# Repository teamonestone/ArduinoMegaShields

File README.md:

# Arduino Mega Shields
Shields for the Arduino Mega.

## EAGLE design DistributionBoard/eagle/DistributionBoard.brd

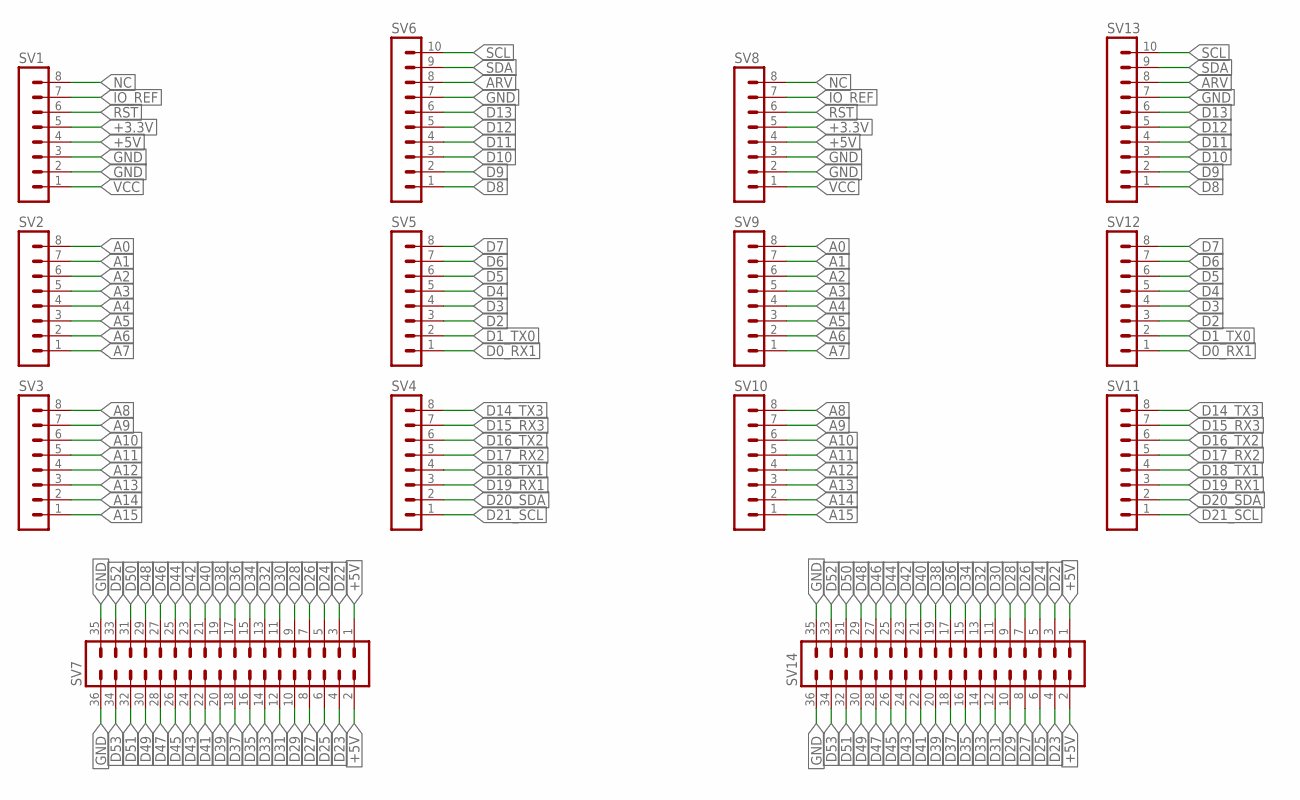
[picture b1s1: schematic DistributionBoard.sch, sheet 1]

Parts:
SV1, SV2, SV3, SV4, SV5, SV8, SV9, SV10, SV11, SV12: MA08-1
SV6, SV13: MA10-1
SV7, SV14: MA18-2

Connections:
+3.3V: SV1.5, SV8.5
+5V: SV1.4, SV7.1, SV7.2, SV8.4, SV14.1, SV14.2; also elsewhere on the board
A0: SV2.8, SV9.8
A1: SV2.7, SV9.7
A2: SV2.6, SV9.6
A3: SV2.5, SV9.5
A4: SV2.4, SV9.4
A5: SV2.3, SV9.3
A6: SV2.2, SV9.2
A7: SV2.1, SV9.1
A8: SV3.8, SV10.8
A9: SV3.7, SV10.7
A10: SV3.6, SV10.6; also elsewhere on the board
A11: SV3.5, SV10.5; also elsewhere on the board
A12: SV3.4, SV10.4; also elsewhere on the board
A13: SV3.3, SV10.3; also elsewhere on the board
A14: SV3.2, SV10.2; also elsewhere on the board
A15: SV3.1, SV10.1; also elsewhere on the board
ARV: SV6.8, SV13.8
D0_RX1: SV5.1, SV12.1
D1_TX0: SV5.2, SV12.2
D2: SV5.3, SV12.3
D3: SV5.4, SV12.4
D4: SV5.5, SV12.5
D5: SV5.6, SV12.6
D6: SV5.7, SV12.7
D7: SV5.8, SV12.8
D8: SV6.1, SV13.1
D9: SV6.2, SV13.2; also elsewhere on the board
D10: SV6.3, SV13.3; also elsewhere on the board
D11: SV6.4, SV13.4; also elsewhere on the board
D12: SV6.5, SV13.5; also elsewhere on the board
D13: SV6.6, SV13.6
D14_TX3: SV4.8, SV11.8
D15_RX3: SV4.7, SV11.7
D16_TX2: SV4.6, SV11.6
D17_RX2: SV4.5, SV11.5
D18_TX1: SV4.4, SV11.4
D19_RX1: SV4.3, SV11.3
D20_SDA: SV4.2, SV11.2; also elsewhere on the board
D21_SCL: SV4.1, SV11.1; also elsewhere on the board
D22: SV7.3, SV14.3
D23: SV7.4, SV14.4
D24: SV7.5, SV14.5
D25: SV7.6, SV14.6
D26: SV7.7, SV14.7
D27: SV7.8, SV14.8
D28: SV7.9, SV14.9; also elsewhere on the board
D29: SV7.10, SV14.10; also elsewhere on the board
D30: SV7.11, SV14.11; also elsewhere on the board
D31: SV7.12, SV14.12; also elsewhere on the board
D32: SV7.13, SV14.13; also elsewhere on the board
D33: SV7.14, SV14.14; also elsewhere on the board
D34: SV7.15, SV14.15; also elsewhere on the board
D35: SV7.16, SV14.16; also elsewhere on the board
D36: SV7.17, SV14.17; also elsewhere on the board
D37: SV7.18, SV14.18; also elsewhere on the board
D38: SV7.19, SV14.19
D39: SV7.20, SV14.20
D40: SV7.21, SV14.21; also elsewhere on the board
D41: SV7.22, SV14.22; also elsewhere on the board
D42: SV7.23, SV14.23; also elsewhere on the board
D43: SV7.24, SV14.24; also elsewhere on the board
D44: SV7.25, SV14.25; also elsewhere on the board
D45: SV7.26, SV14.26; also elsewhere on the board
D46: SV7.27, SV14.27; also elsewhere on the board
D47: SV7.28, SV14.28; also elsewhere on the board
D48: SV7.29, SV14.29; also elsewhere on the board
D49: SV7.30, SV14.30; also elsewhere on the board
D50: SV7.31, SV14.31; also elsewhere on the board
D51: SV7.32, SV14.32; also elsewhere on the board
D52: SV7.33, SV14.33; also elsewhere on the board
D53: SV7.34, SV14.34
GND: SV1.2, SV1.3, SV6.7, SV7.35, SV7.36, SV8.2, SV8.3, SV13.7, SV14.35, SV14.36; also elsewhere on the board
IO_REF: SV1.7, SV8.7
NC: SV1.8, SV8.8
RST: SV1.6, SV8.6; also elsewhere on the board
SCL: SV6.10, SV13.10
SDA: SV6.9, SV13.9
VCC: SV1.1, SV8.1; also elsewhere on the board

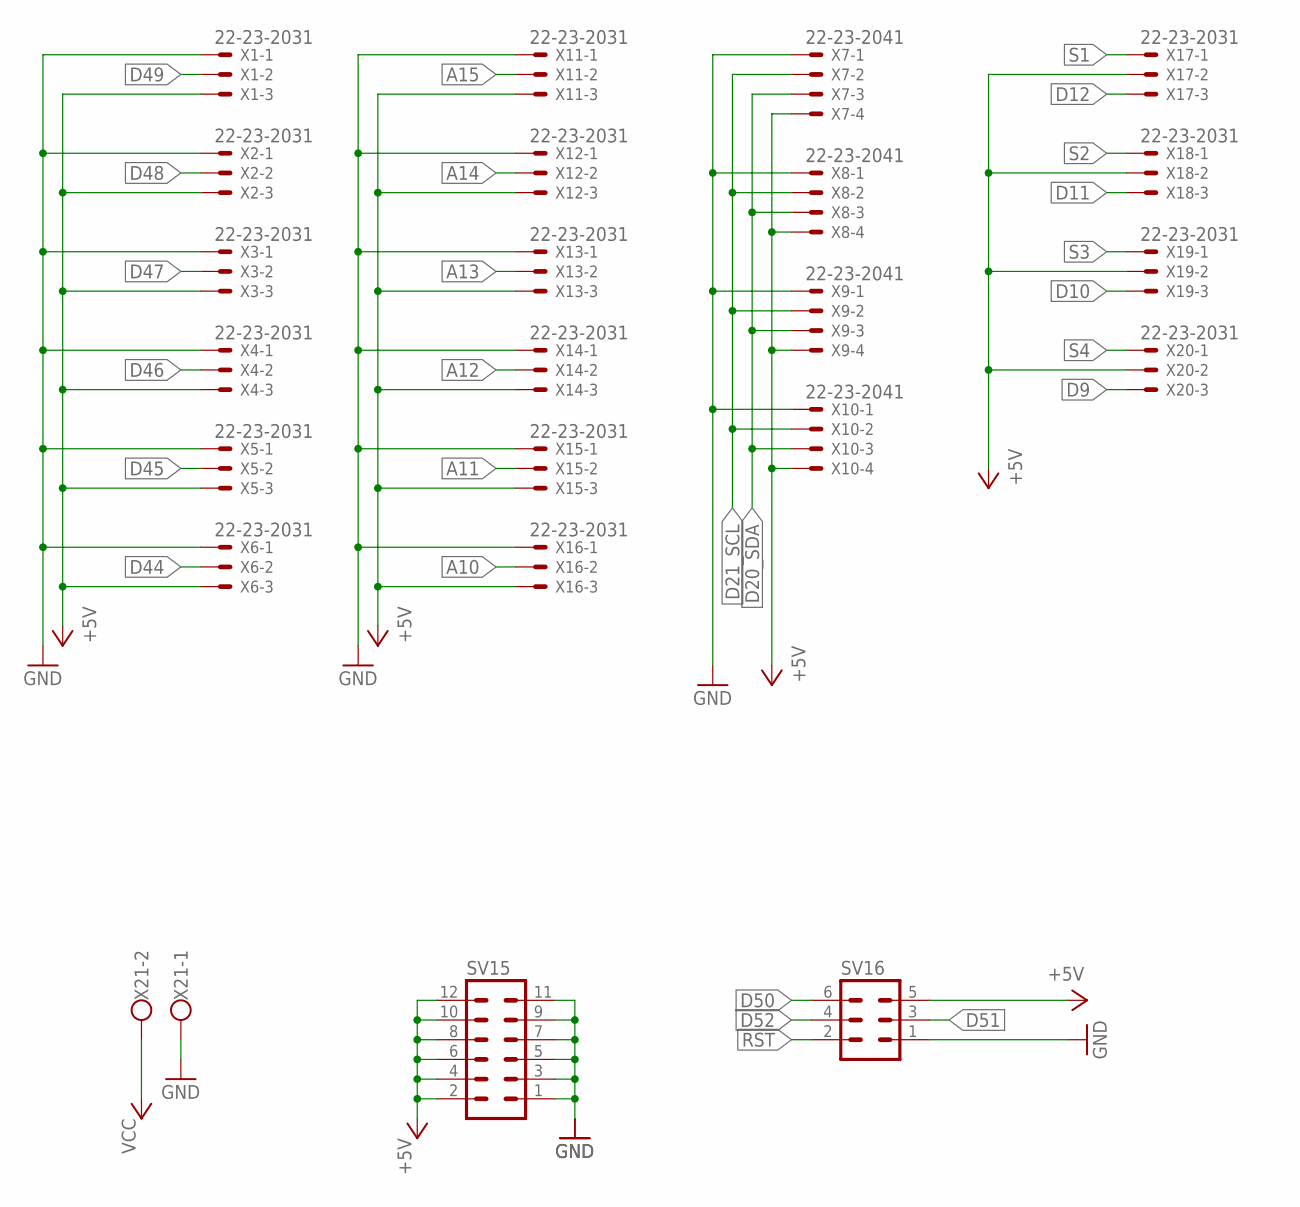
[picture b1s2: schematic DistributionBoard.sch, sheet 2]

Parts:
SV15: MA06-2
SV16: MA03-2
X1, X2, X3, X4, X5, X6, X11, X12, X13, X14, X15, X16, X17, X18, X19, X20: 22-23-2031
X7, X8, X9, X10: 22-23-2041
X21: W237-102

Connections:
+5V: SV15.2, SV15.4, SV15.6, SV15.8, SV15.10, SV15.12, SV16.5, X1.3, X2.3, X3.3, X4.3, X5.3, X6.3, X7.4, X8.4, X9.4, X10.4, X11.3, X12.3, X13.3, X14.3, X15.3, X16.3, X17.2, X18.2, X19.2, X20.2; also elsewhere on the board
A10: X16.2; also elsewhere on the board
A11: X15.2; also elsewhere on the board
A12: X14.2; also elsewhere on the board
A13: X13.2; also elsewhere on the board
A14: X12.2; also elsewhere on the board
A15: X11.2; also elsewhere on the board
D9: X20.3; also elsewhere on the board
D10: X19.3; also elsewhere on the board
D11: X18.3; also elsewhere on the board
D12: X17.3; also elsewhere on the board
D20_SDA: X7.3, X8.3, X9.3, X10.3; also elsewhere on the board
D21_SCL: X7.2, X8.2, X9.2, X10.2; also elsewhere on the board
D44: X6.2; also elsewhere on the board
D45: X5.2; also elsewhere on the board
D46: X4.2; also elsewhere on the board
D47: X3.2; also elsewhere on the board
D48: X2.2; also elsewhere on the board
D49: X1.2; also elsewhere on the board
D50: SV16.6; also elsewhere on the board
D51: SV16.3; also elsewhere on the board
D52: SV16.4; also elsewhere on the board
GND: SV15.1, SV15.3, SV15.5, SV15.7, SV15.9, SV15.11, SV16.1, X1.1, X2.1, X3.1, X4.1, X5.1, X6.1, X7.1, X8.1, X9.1, X10.1, X11.1, X12.1, X13.1, X14.1, X15.1, X16.1, X21.1; also elsewhere on the board
RST: SV16.2; also elsewhere on the board
S1: X17.1; also elsewhere on the board
S2: X18.1; also elsewhere on the board
S3: X19.1; also elsewhere on the board
S4: X20.1; also elsewhere on the board
VCC: X21.2; also elsewhere on the board

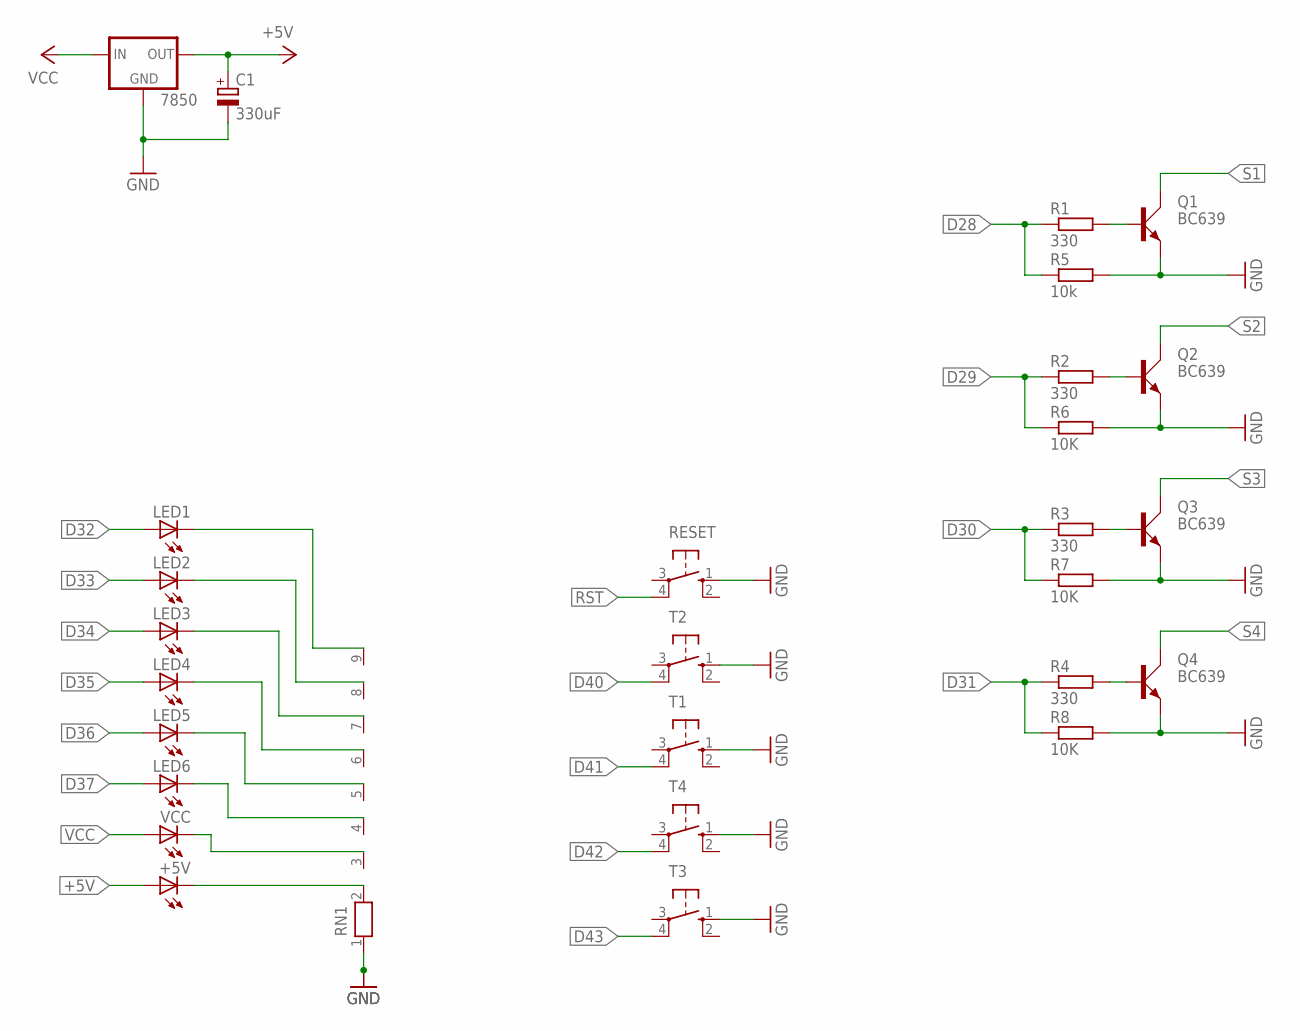
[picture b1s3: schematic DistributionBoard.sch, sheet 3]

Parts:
7850: 78XXS
+5V: LED3MM
C1: 330uF; E3,5-8
LED1, LED2, LED3, LED4, LED5, LED6: LED3MM
Q1, Q2, Q3, Q4: BC639; SOT54D
R1, R2, R3, R4: 330; M1206
R5: 10k; M1206
R6, R7, R8: 10K; M1206
RESET: 10-XX; B3F-10XX
RN1: RN08; RN-9
T1, T2, T3, T4: 10-XX; B3F-10XX
VCC: LED3MM

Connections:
+5V: 7850.OUT, +5V.A, C1.+; also elsewhere on the board
D28: R1.1, R5.1; also elsewhere on the board
D29: R2.1, R6.1; also elsewhere on the board
D30: R3.1, R7.1; also elsewhere on the board
D31: R4.1, R8.1; also elsewhere on the board
D32: LED1.A; also elsewhere on the board
D33: LED2.A; also elsewhere on the board
D34: LED3.A; also elsewhere on the board
D35: LED4.A; also elsewhere on the board
D36: LED5.A; also elsewhere on the board
D37: LED6.A; also elsewhere on the board
D40: T2.4 (P1); also elsewhere on the board
D41: T1.4 (P1); also elsewhere on the board
D42: T4.4 (P1); also elsewhere on the board
D43: T3.4 (P1); also elsewhere on the board
GND: 7850.GND, C1.-, Q1.E, Q2.E, Q3.E, Q4.E, R5.2, R6.2, R7.2, R8.2, RESET.1 (S), RN1.1, T1.1 (S), T2.1 (S), T3.1 (S), T4.1 (S); also elsewhere on the board
unnamed: +5V.K (C), RN1.2
unnamed: RN1.3, VCC.K (C)
unnamed: LED6.K (C), RN1.4
unnamed: LED5.K (C), RN1.5
unnamed: LED4.K (C), RN1.6
unnamed: LED3.K (C), RN1.7
unnamed: LED2.K (C), RN1.8
unnamed: LED1.K (C), RN1.9
unnamed: Q4.B, R4.2
unnamed: Q3.B, R3.2
unnamed: Q2.B, R2.2
unnamed: Q1.B, R1.2
RST: RESET.4 (P1); also elsewhere on the board
S1: Q1.C; also elsewhere on the board
S2: Q2.C; also elsewhere on the board
S3: Q3.C; also elsewhere on the board
S4: Q4.C; also elsewhere on the board
VCC: 7850.IN, VCC.A; also elsewhere on the board

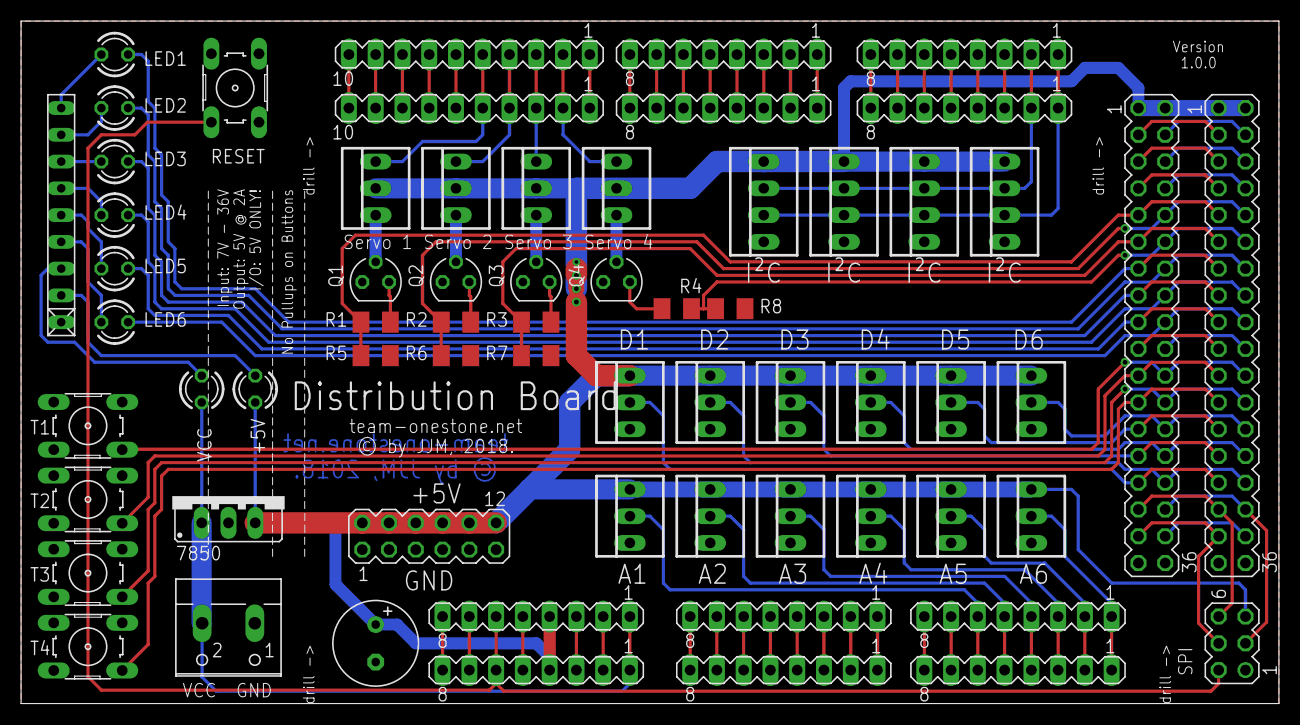
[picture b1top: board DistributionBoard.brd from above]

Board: 2 copper layers, 119.4 x 64.8 mm, 65 parts (0 on the bottom side), 96 nets.

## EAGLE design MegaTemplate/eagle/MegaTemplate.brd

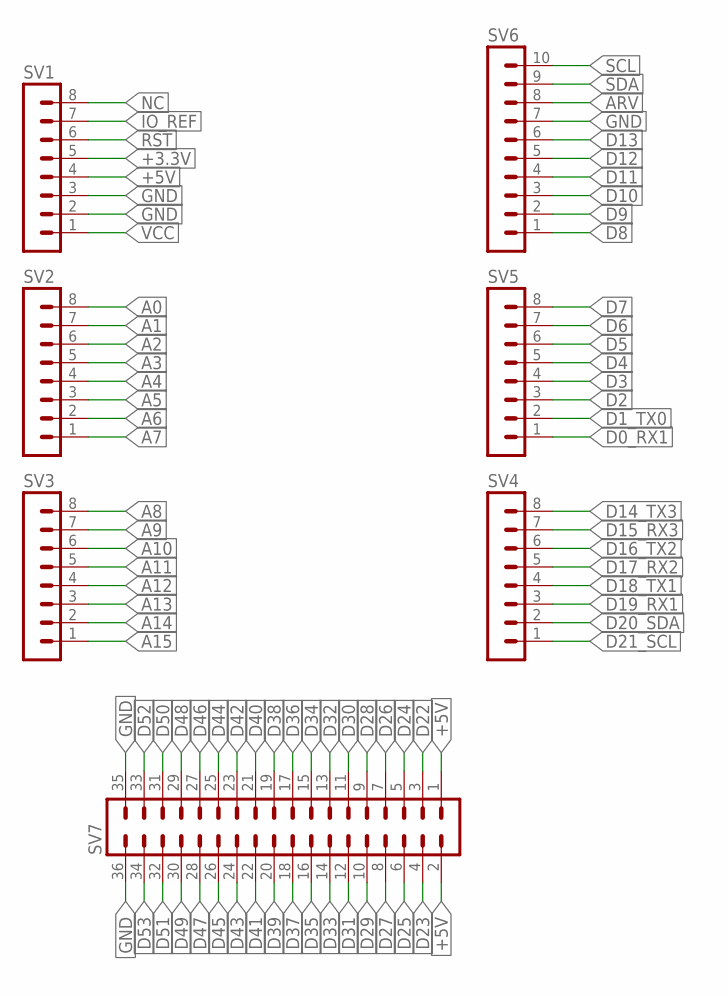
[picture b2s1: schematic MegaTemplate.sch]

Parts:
SV1, SV2, SV3, SV4, SV5: MA08-1
SV6: MA10-1
SV7: MA18-2

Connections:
+3.3V: SV1.5
+5V: SV1.4, SV7.1, SV7.2
A0: SV2.8
A1: SV2.7
A2: SV2.6
A3: SV2.5
A4: SV2.4
A5: SV2.3
A6: SV2.2
A7: SV2.1
A8: SV3.8
A9: SV3.7
A10: SV3.6
A11: SV3.5
A12: SV3.4
A13: SV3.3
A14: SV3.2
A15: SV3.1
ARV: SV6.8
D0_RX1: SV5.1
D1_TX0: SV5.2
D2: SV5.3
D3: SV5.4
D4: SV5.5
D5: SV5.6
D6: SV5.7
D7: SV5.8
D8: SV6.1
D9: SV6.2
D10: SV6.3
D11: SV6.4
D12: SV6.5
D13: SV6.6
D14_TX3: SV4.8
D15_RX3: SV4.7
D16_TX2: SV4.6
D17_RX2: SV4.5
D18_TX1: SV4.4
D19_RX1: SV4.3
D20_SDA: SV4.2
D21_SCL: SV4.1
D22: SV7.3
D23: SV7.4
D24: SV7.5
D25: SV7.6
D26: SV7.7
D27: SV7.8
D28: SV7.9
D29: SV7.10
D30: SV7.11
D31: SV7.12
D32: SV7.13
D33: SV7.14
D34: SV7.15
D35: SV7.16
D36: SV7.17
D37: SV7.18
D38: SV7.19
D39: SV7.20
D40: SV7.21
D41: SV7.22
D42: SV7.23
D43: SV7.24
D44: SV7.25
D45: SV7.26
D46: SV7.27
D47: SV7.28
D48: SV7.29
D49: SV7.30
D50: SV7.31
D51: SV7.32
D52: SV7.33
D53: SV7.34
GND: SV1.2, SV1.3, SV6.7, SV7.35, SV7.36
IO_REF: SV1.7
NC: SV1.8
RST: SV1.6
SCL: SV6.10
SDA: SV6.9
VCC: SV1.1

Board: 2 copper layers, 7 parts (0 on the bottom side), 2 nets, no tracks yet.

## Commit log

2018-11-09 Schaltplan fertig
2018-11-13 Template for Arduino Mega Shields
2018-11-23 fixed pin header orientation
2018-11-23 Ausrichtung vom Text gefixed
2018-11-23 Grundaufbau für Distibution Board
2018-11-23 Distribution Board
2018-11-26 Distribution Board fertig
2018-11-26 prod version

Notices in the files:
DistributionBoard/eagle/DistributionBoard.brd:
© by JJM, 2018.
